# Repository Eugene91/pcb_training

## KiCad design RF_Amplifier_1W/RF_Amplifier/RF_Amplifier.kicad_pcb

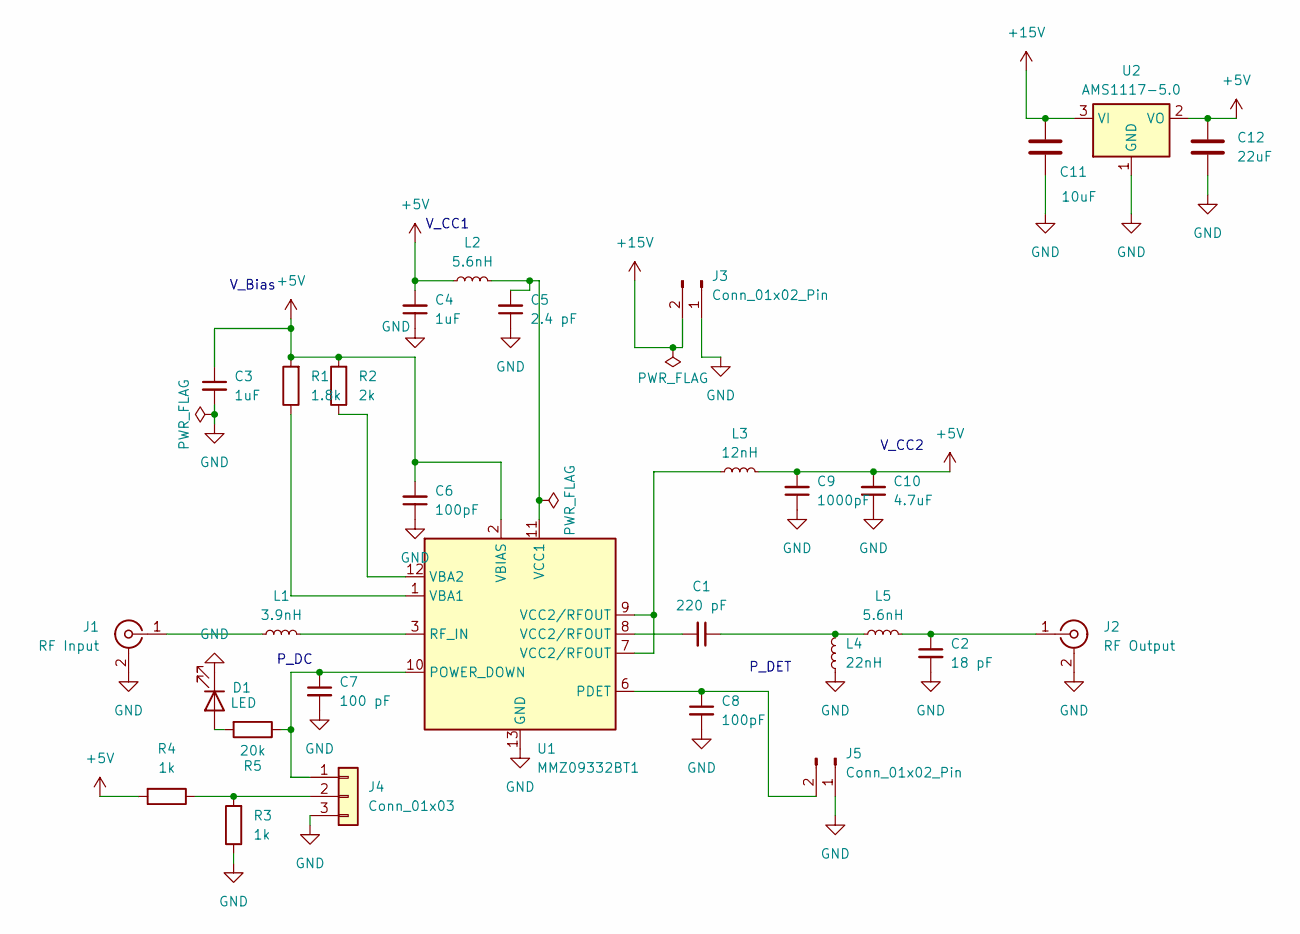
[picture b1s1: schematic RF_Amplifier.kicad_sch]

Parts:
C1: 220 pF; C_1206_3216Metric
C2: 18 pF; C_0805_2012Metric
C3, C4: 1uF; C_1206_3216Metric
C5: 2.4 pF; C_0805_2012Metric
C6, C8: 100pF; C_1206_3216Metric
C7: 100 pF; C_0805_2012Metric
C9: 1000pF; C_1206_3216Metric
C10: 4.7uF; C_1206_3216Metric
C11: 10uF; C_1206_3216Metric
C12: 22uF; C_1206_3216Metric
D1: LED; LED_1206_3216Metric
J1: RF Input; CONN_73137-5003_MOL
J2: RF Output; CONN_73137-5003_MOL
J3, J5: Conn_01x02_Pin; PinHeader_1x02_P2.54mm_Vertical
J4: Conn_01x03; PinHeader_1x03_P2.54mm_Vertical
L1: 3.9nH; L_0805_2012Metric
L2, L5: 5.6nH; L_0805_2012Metric
L3: 12nH; L_0805_2012Metric
L4: 22nH; L_0805_2012Metric
R1: 1.8k; R_1206_3216Metric
R2: 2k; R_1206_3216Metric
R3, R4: 1k; R_1206_3216Metric
R5: 20k; R_1206_3216Metric
U1: MMZ09332BT1; QFN-12-1EP_3x3mm_P0.5mm_EP1.6x1.6mm_ThermalVias
U2: AMS1117-5.0; SOT-223-3_TabPin2

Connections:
+5V: C3.1, C4.2, C6.2, C9.2, C10.2, C12.1, L2.1, L3.2, R1.2, R2.2, R4.2, U1.2 (VBIAS), U2.2 (VO)
+15V: C11.1, J3.2, U2.3 (VI)
GND: C2.2, C3.2, C4.1, C5.1, C6.1, C7.2, C8.2, C9.1, C10.1, C11.2, C12.2, D1.1 (K), J1.2 (Ext), J2.2 (Ext), J3.1, J4.3, J5.1, L4.1, R3.1, U1.13 (GND), U2.1 (GND)
unnamed: C1.1, L4.2, L5.1
unnamed: C1.2, U1.8 (VCC2/RFOUT)
unnamed: D1.2 (A), R5.2
unnamed: J1.1 (In), L1.1
unnamed: C2.1, J2.1 (In), L5.2
unnamed: C7.1, J4.1, R5.1, U1.10 (POWER_DOWN)
unnamed: J4.2, R3.2, R4.1
unnamed: C8.1, J5.2, U1.6 (PDET)
unnamed: L3.1, U1.7 (VCC2/RFOUT), U1.9 (VCC2/RFOUT)
unnamed: L1.2, U1.3 (RF_IN)
unnamed: R1.1, U1.1 (VBA1)
unnamed: R2.1, U1.12 (VBA2)
unnamed: C5.2, L2.2, U1.11 (VCC1)

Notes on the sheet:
V_CC1
V_CC2
P_DET
P_DC
V_Bias

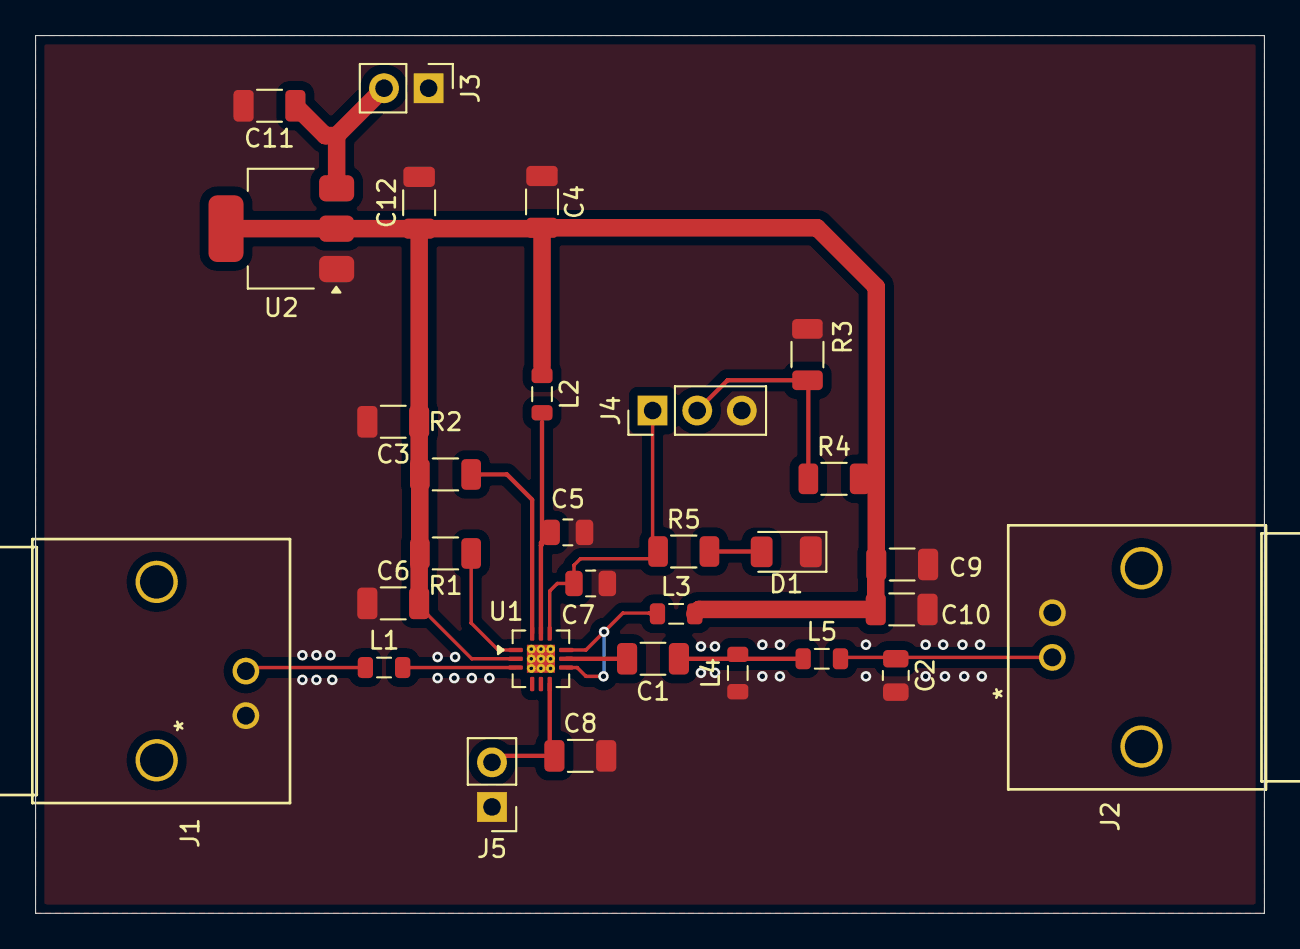
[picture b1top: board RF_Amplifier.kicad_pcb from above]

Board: 2 copper layers, 70.0 x 50.0 mm, 30 parts (0 on the bottom side), 16 nets.

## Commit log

2025-11-05 BOM and Board are added
2025-11-10 Zhongan's test PCB
    Wirebonding pads for 10 heaters traced to a connector
2025-11-12 Add files via upload
    Add the project files.
2025-11-14 See previous update
2026-01-08 The version of the board that went into production
